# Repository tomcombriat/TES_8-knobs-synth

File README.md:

# TES - 8 knobs synth
T. Combriat

8 knobs synths are simple synthesizers based on [Mozzi](https://github.com/sensorium/Mozzi) using STM32 blue pill as the main hardware. Thanks to the computing power of these chips, these synthesizers are able to generate complex polyphonic sounds at 32kHz sampling rate. The aim of this serie is to provide a fixed hardware which can be used for different synthesis methods.

### Synthesizers
* [XORAND](XORAND_poly)
* [FM synth](FM_synth_poly)

***

### Hardware
These synthesizers feature: 
* MIDI input and thru
* 8 knobs for controlling parameters (thus the name), note that one is hardwired for volume control
* 6.35mm audio output (mono)
* standalone power from 3 AA batteries. This ensures cleaner sound thanks to very stable power lines.

PCBs for the chip are single faced and can be easily made if one is able to make 250 microns wide tracks. The mask is provided [here](8knobs_mono) for the mono version.

#### Hardware versions
For now, only one version of this synth has been developped: mono output using the chip PWM and a low-pass 1<sup>st</sup> filter. Other versions, featuring Mozzi HiFi, stereo, DAC outputs may come.

***

### Programming
These synths can be programmed like any other STM32 pills using USB to serial converter. Native USB will usually not work. You will  also need a rather new version of the Arduino IDE with Mozzi installed and modify Mozzi in accordance with the beginning of the sketch or use the [TES forked version of Mozzi](https://github.com/tomcombriat/Mozzi/tree/TES-stable).

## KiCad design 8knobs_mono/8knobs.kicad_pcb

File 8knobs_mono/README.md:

## 8 knobs mono

Actual working version of 8 knobs synth. Features an STM32 BluePill, with standard audio output (STANDARD_PLUS 10bits of Mozzi @ 32k)

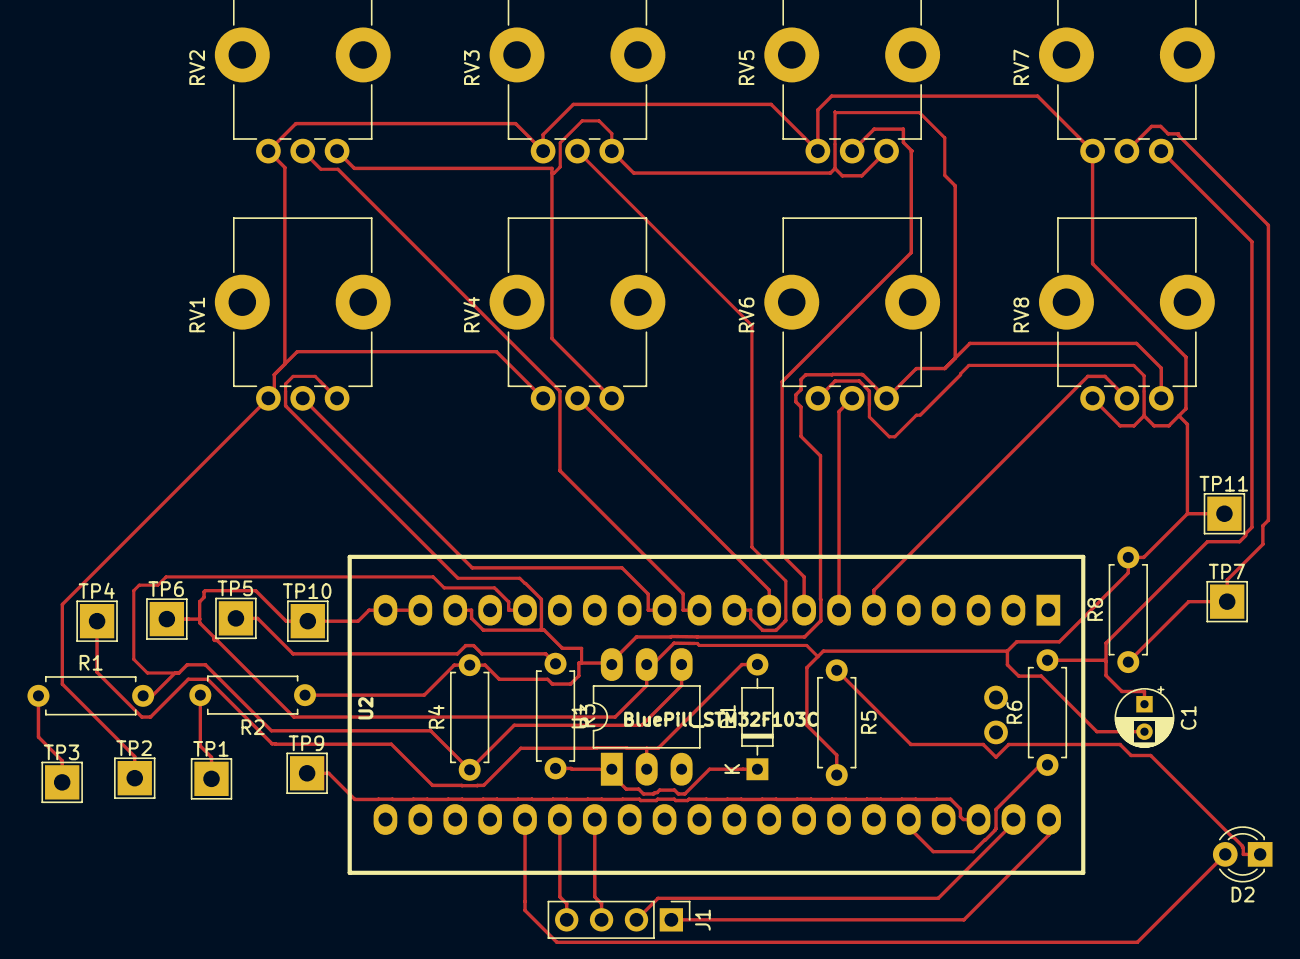
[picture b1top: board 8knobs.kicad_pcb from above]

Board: 2 copper layers, 31 parts (0 on the bottom side), 25 nets.

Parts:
C1: 10n; CP_Radial_D4.0mm_P2.00mm
D1: 1N914; D_DO-35_SOD27_P7.62mm_Horizontal
D2: LED; LED_D3.0mm
J1: Conn_01x04_Female; PinHeader_1x04_P2.54mm_Vertical
R1: 10; R_Axial_DIN0207_L6.3mm_D2.5mm_P7.62mm_Horizontal
R2: 33; R_Axial_DIN0207_L6.3mm_D2.5mm_P7.62mm_Horizontal
R3, R4, R5: 220; R_Axial_DIN0207_L6.3mm_D2.5mm_P7.62mm_Horizontal
R6: 470; R_Axial_DIN0207_L6.3mm_D2.5mm_P7.62mm_Horizontal
R8: 1k; R_Axial_DIN0207_L6.3mm_D2.5mm_P7.62mm_Horizontal
RV1, RV2, RV3, RV4, RV5, RV6, RV7, RV8: 10K; Potentiometer_Alps_RK09K_Single_Vertical
TP1: T4; TestPoint_THTPad_2.5x2.5mm_Drill1.2mm
TP2: T2; TestPoint_THTPad_2.5x2.5mm_Drill1.2mm
TP3: T5; TestPoint_THTPad_2.5x2.5mm_Drill1.2mm
TP4: IN5; TestPoint_THTPad_2.5x2.5mm_Drill1.2mm
TP5: IN4; TestPoint_THTPad_2.5x2.5mm_Drill1.2mm
TP6: IN2; TestPoint_THTPad_2.5x2.5mm_Drill1.2mm
TP7: out1; TestPoint_THTPad_2.5x2.5mm_Drill1.2mm
TP9: Batt+; TestPoint_THTPad_2.5x2.5mm_Drill1.2mm
TP10: Batt-; TestPoint_THTPad_2.5x2.5mm_Drill1.2mm
TP11: GND; TestPoint_THTPad_2.5x2.5mm_Drill1.2mm
U1: PC900
U2: BluePill_STM32F103C

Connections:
+3V3: R2.1, R4.2, RV1.1, RV2.1, RV3.1, RV4.1, RV5.1, RV6.1, RV8.1, U1.6, U2.18
GND: C1.2, R5.2, R8.2, RV1.3, RV2.3, RV3.3, RV4.3, RV5.3, RV6.3, RV7.3, RV8.3, TP2.1, TP6.1, TP10.1, TP11.1, U1.5, U2.19, U2.20
unnamed: C1.1, R6.2, RV7.1
unnamed: D1.1, R3.2, U1.1
unnamed: D1.2, TP4.1, U1.2
unnamed: D2.1, R5.1
unnamed: D2.2, U2.25
unnamed: J1.1, U2.40
unnamed: J1.2, U2.39
unnamed: J1.3, U2.27
unnamed: J1.4, U2.26
unnamed: R1.1, TP3.1
unnamed: R1.2, R4.1, U1.4, U2.16
unnamed: R2.2, TP1.1
unnamed: R3.1, TP5.1
unnamed: R6.1, U2.36
unnamed: R8.1, RV7.2, TP7.1
unnamed: RV1.2, U2.12
unnamed: RV2.2, U2.11
unnamed: RV3.2, U2.10
unnamed: RV4.2, U2.9
unnamed: RV5.2, U2.8
unnamed: RV6.2, U2.7
unnamed: RV8.2, U2.6
unnamed: TP9.1, U2.38

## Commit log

2019-06-24 Add kicad files
2019-06-24 first test with arduino -> LPF not low enough
2019-06-24 removed weird folder
2019-06-25 FM synth, start
2019-07-07 Added polyphony to FM synth
2019-07-09 Sustain supported
2019-07-09 Add second LFO
2019-07-11 Soft clip and note velocity taken into account
2019-07-11 Add second (square) sub-oscilator
2019-08-09 Correction to FM synth, add of digital_Mix synth
2019-08-09 Suppressed FM_synth monophonic
2019-08-12 Frequency type more accurate
2019-08-12 More conventional envelope
2019-08-12 Added crude wavefolding
2019-08-22 Added Pitchbend support and aftertouch, cleaned code
2019-08-23 PB correction
2019-09-01 Renamed digital_mix XOrand Pitchbend and aftertouch added
2019-09-01 removed digital_mix
2019-09-03 Final version ?
2019-09-20 Sax (EWI) version of XORAND, corrected scheduler of XORAND, corrected fabrication mask
2019-10-07 v1.1 of 8knobs mono: - corrected wrong connection to battery - easier PCB manufacturing
2019-10-23 update to v1.1 for PCB mask
2019-11-21 Corrected header in XORAND Corrected unwanted access to serial in Xorand
2020-01-10 Added license
2020-01-22 typo
2020-01-22 Removed old version
2020-02-18 Modified LFO for vibrato, check for overflow before reverb
2020-03-05 Modified vibrato: faster, smaller
2020-04-07 Switched to no_alia saw wave
2020-04-07 Added vibrato mode, can be enabled, or not, at the beginning of the sketch
2020-04-07 Increased volume, increased resolution
2020-04-15 Add 8k_sax with chords ability (pol 4)
2020-04-15 Added different LED behavior on startup to differentiate the two versions of XORAND_SAX
2020-04-19 Added attack and release parameters for chords notes (when adding another note to a playing one)
2020-05-01 Added pitchbend amplitude to XORAND_sax(s)
2020-05-02 Notes on release phase are shutdwon definitively on breath=0
2020-05-03 Simplified midi_handles of noteOn
2020-05-24 Replaced chord_attack, broken by previous commit
2020-05-30 Enhanced chord behavior
2020-05-30 Added comments about latch and so
2020-05-31 Faster on MIDI, now taking chords notes on different channel
2020-05-31 Non lagging sax chord
2020-05-31 Separated all functions in updateControl()
2020-05-31 A lot of oscil!
2020-06-10 Update FM_synth_poly.ino
    Added braces to fix compile error
2020-06-15 Update XORAND_poly.ino
    Adjusted serial port to match schematic
2020-06-15 Update FM_synth_poly.ino
    Updated serial port to match schematic
2020-06-15 Update XORAND_sax.ino
    Updated serial port to match schematic
2020-06-15 Update XORAND_sax_chord.ino
    Updated serial port to match schematic
